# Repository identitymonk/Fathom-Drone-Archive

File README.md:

# Fathom-Drone-Archive
Archive of the dead Fathom Drone Project (https://www.kickstarter.com/projects/1359605477/fathom-one-the-affordable-modular-hd-underwater-dr)

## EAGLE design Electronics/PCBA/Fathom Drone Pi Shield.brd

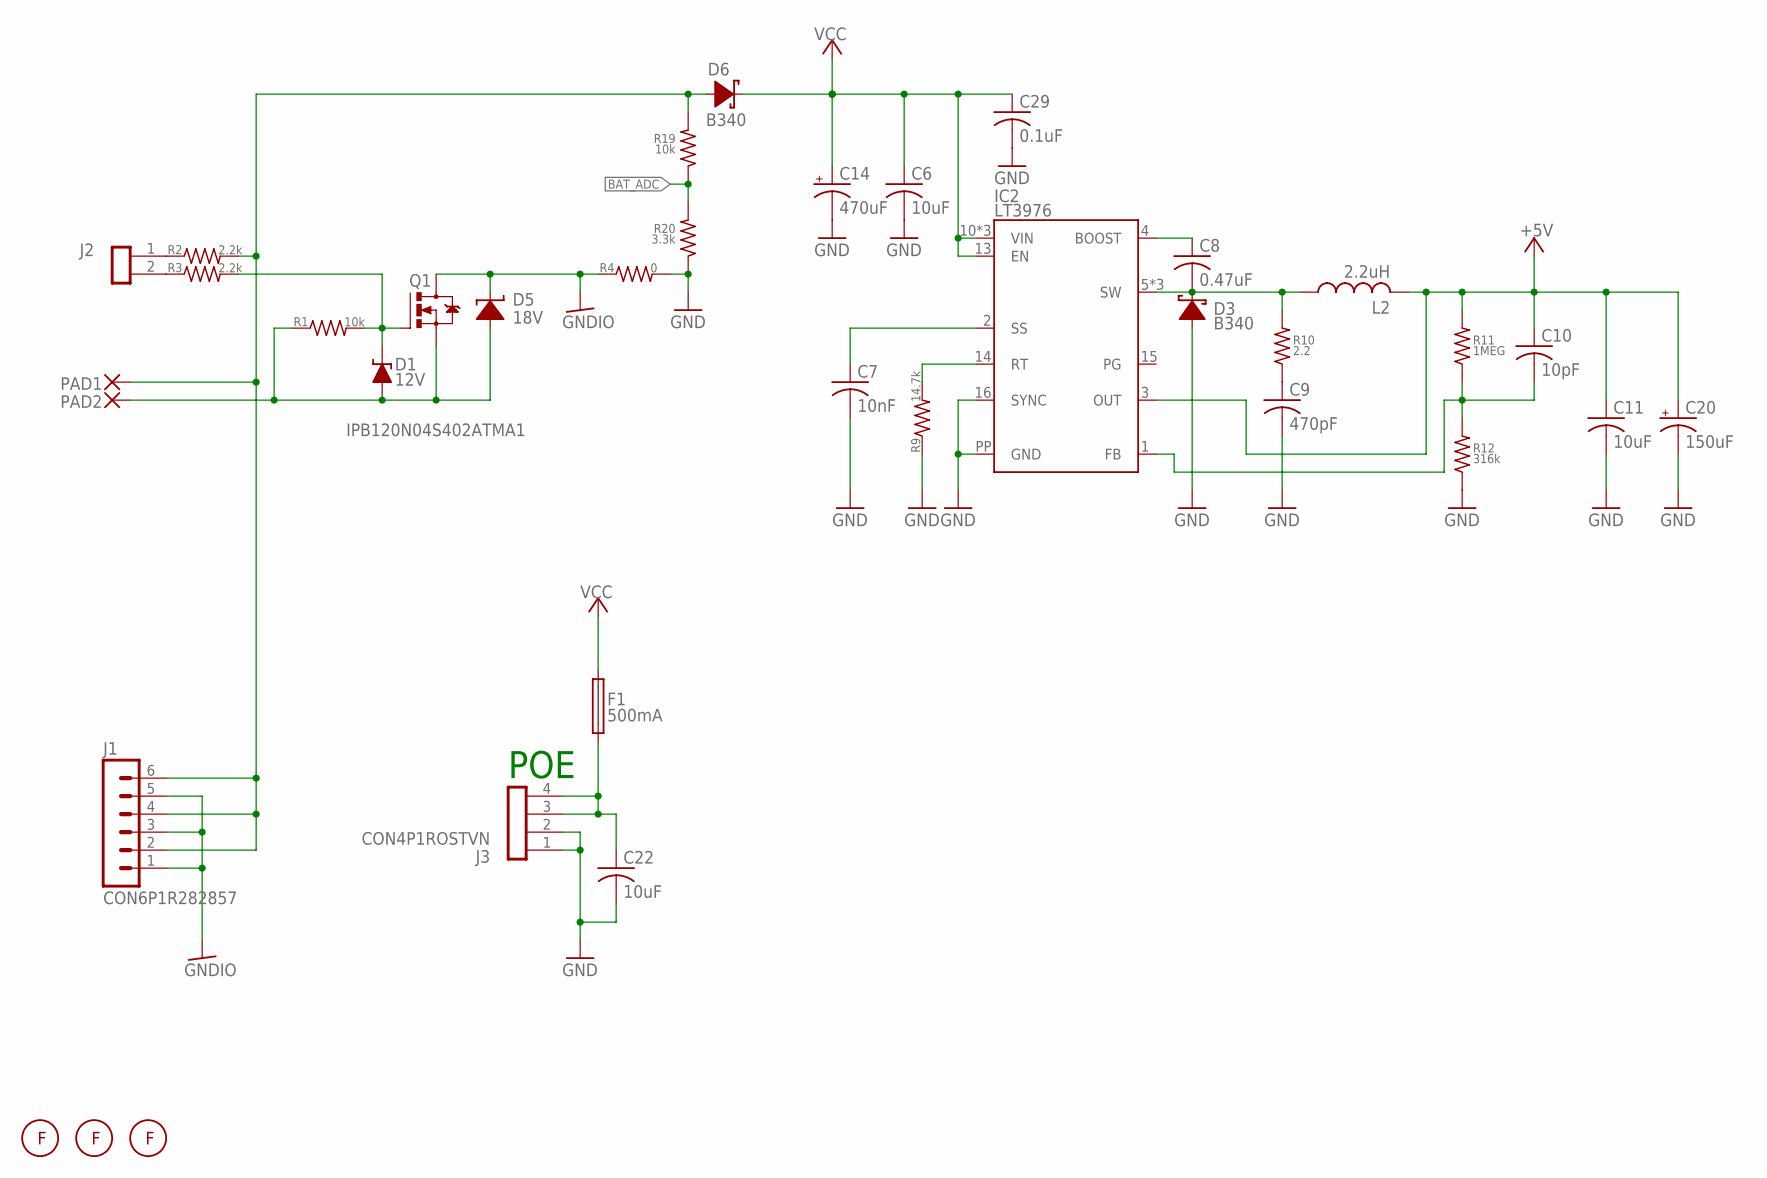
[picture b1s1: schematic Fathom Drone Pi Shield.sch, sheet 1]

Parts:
C6, C22: 10uF; C1206
C7: 10nF; C0402
C8: 0.47uF; C0603
C9: 470pF; C0603
C10: 10pF; C0603
C11: 10uF; C0805
C14: 470uF; E3,5-8
C20: 150uF; PANASONIC_C
C29: 0.1uF; C0402
D1: 12V; SOT-23
D3, D6: B340; SMA
D5: 18V; SMC
F1: 500mA; BETTER_LITTELFUSE1812
FM1, FM2, FM3: FIDUCIAL1MM; 1MMCIRCLE
IC2: LT3976; MSOP-16-PP
J1: CON6P1R282857; 282857-6
J2: CON2P1ROSTVN; OSTVN02A150
J3: CON4P1ROSTVN; OSTVN04A150
L2: 2.2uH; VLP8040
PAD1, PAD2: WIREPAD5.5/3,0; 5.5/3,0
Q1: IPB120N04S402ATMA1; TO263
R1, R19: 10k; R0603
R2, R3: 2.2k; R0603
R4: 0; R0805
R9: 14.7k; R0603
R10: 2.2; R0603
R11: 1MEG; R0603
R12: 316k; R0603
R20: 3.3k; R0402

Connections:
+5V: C10.1, C11.1, C20.+, IC2.3 (OUT), L2.P$2 (2), R11.2; also elsewhere on the board
BAT_ADC: R19.1, R20.2; also elsewhere on the board
GND: C6.2, C7.2, C9.2, C11.2, C14.-, C20.-, C22.2, C29.2, D3.A, IC2.16 (SYNC), IC2.PP (GND), J3.1, J3.2, R4.2, R9.1, R12.1, R20.1; also elsewhere on the board
GNDIO: D5.C, J1.1, J1.3, J1.5, Q1.3 (D), R4.1
unnamed: D1.1 (A), D5.A, PAD2.P$1, Q1.2 (S), R1.1
unnamed: J2.1, R2.1
unnamed: J2.2, R3.1
unnamed: D6.A, J1.2, J1.4, J1.6, PAD1.P$1, R2.2, R19.2
unnamed: C7.1, IC2.2 (SS)
unnamed: IC2.14 (RT), R9.2
unnamed: C8.2, D3.C, IC2.5 (SW), IC2.6 (SW), IC2.7 (SW), L2.P$1 (1), R10.2
unnamed: C8.1, IC2.4 (BOOST)
unnamed: C9.1, R10.1
unnamed: C10.2, IC2.1 (FB), R11.1, R12.2
unnamed: D1.3 (K), Q1.1 (G), R1.2, R3.2
unnamed: C22.1, F1.P$1 (1), J3.3, J3.4
VCC: C6.1, C14.+, C29.1, D6.C, F1.P$2 (2), IC2.10 (VIN), IC2.11 (VIN), IC2.12 (VIN), IC2.13 (EN); also elsewhere on the board

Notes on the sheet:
POE

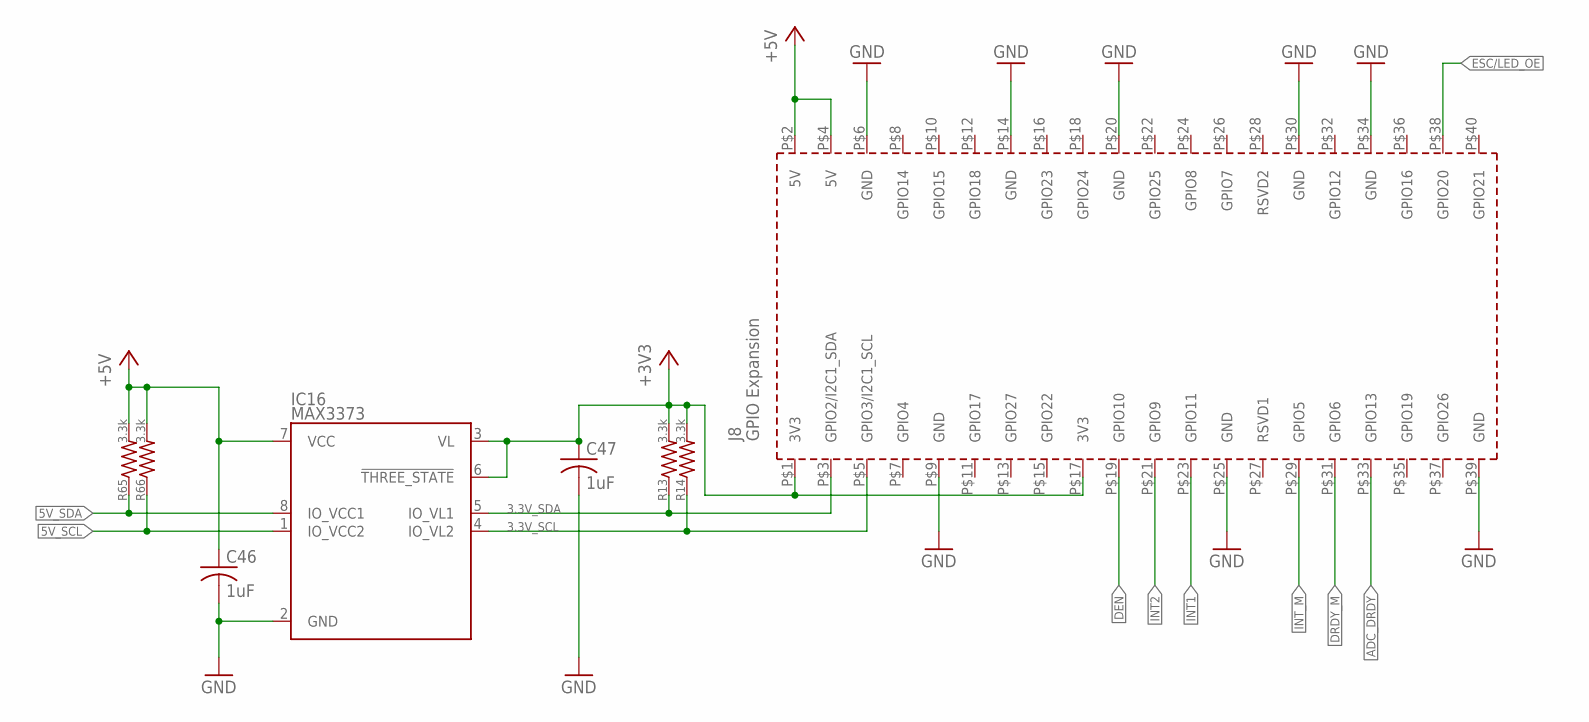
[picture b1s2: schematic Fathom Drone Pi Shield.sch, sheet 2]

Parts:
C46, C47: 1uF; C0402
IC16: MAX3373; TS8
PCB1: RPI3
R13, R14, R65, R66: 3.3k; R0402

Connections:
3.3V_SCL: IC16.4 (IO_VL2), PCB1.P$5 (GPIO3/I2C1_SCL), R14.1; also elsewhere on the board
3.3V_SDA: IC16.5 (IO_VL1), PCB1.P$3 (GPIO2/I2C1_SDA), R13.1; also elsewhere on the board
5V_SCL: IC16.1 (IO_VCC2), R66.1; also elsewhere on the board
5V_SDA: IC16.8 (IO_VCC1), R65.1; also elsewhere on the board
+3V3: C47.1, IC16.3 (VL), IC16.6 (!THREE_STATE), PCB1.P$1 (3V3), PCB1.P$17 (3V3), R13.2, R14.2; also elsewhere on the board
+5V: C46.1, IC16.7 (VCC), PCB1.P$2 (5V), PCB1.P$4 (5V), R65.2, R66.2; also elsewhere on the board
ADC_DRDY: PCB1.P$33 (GPIO13); also elsewhere on the board
DEN: PCB1.P$19 (GPIO10); also elsewhere on the board
DRDY_M: PCB1.P$31 (GPIO6); also elsewhere on the board
ESC/LED_OE: PCB1.P$38 (GPIO20); also elsewhere on the board
GND: C46.2, C47.2, IC16.2 (GND), PCB1.P$6 (GND), PCB1.P$9 (GND), PCB1.P$14 (GND), PCB1.P$20 (GND), PCB1.P$25 (GND), PCB1.P$30 (GND), PCB1.P$34 (GND), PCB1.P$39 (GND); also elsewhere on the board
INT1: PCB1.P$23 (GPIO11); also elsewhere on the board
INT2: PCB1.P$21 (GPIO9); also elsewhere on the board
INT_M: PCB1.P$29 (GPIO5); also elsewhere on the board

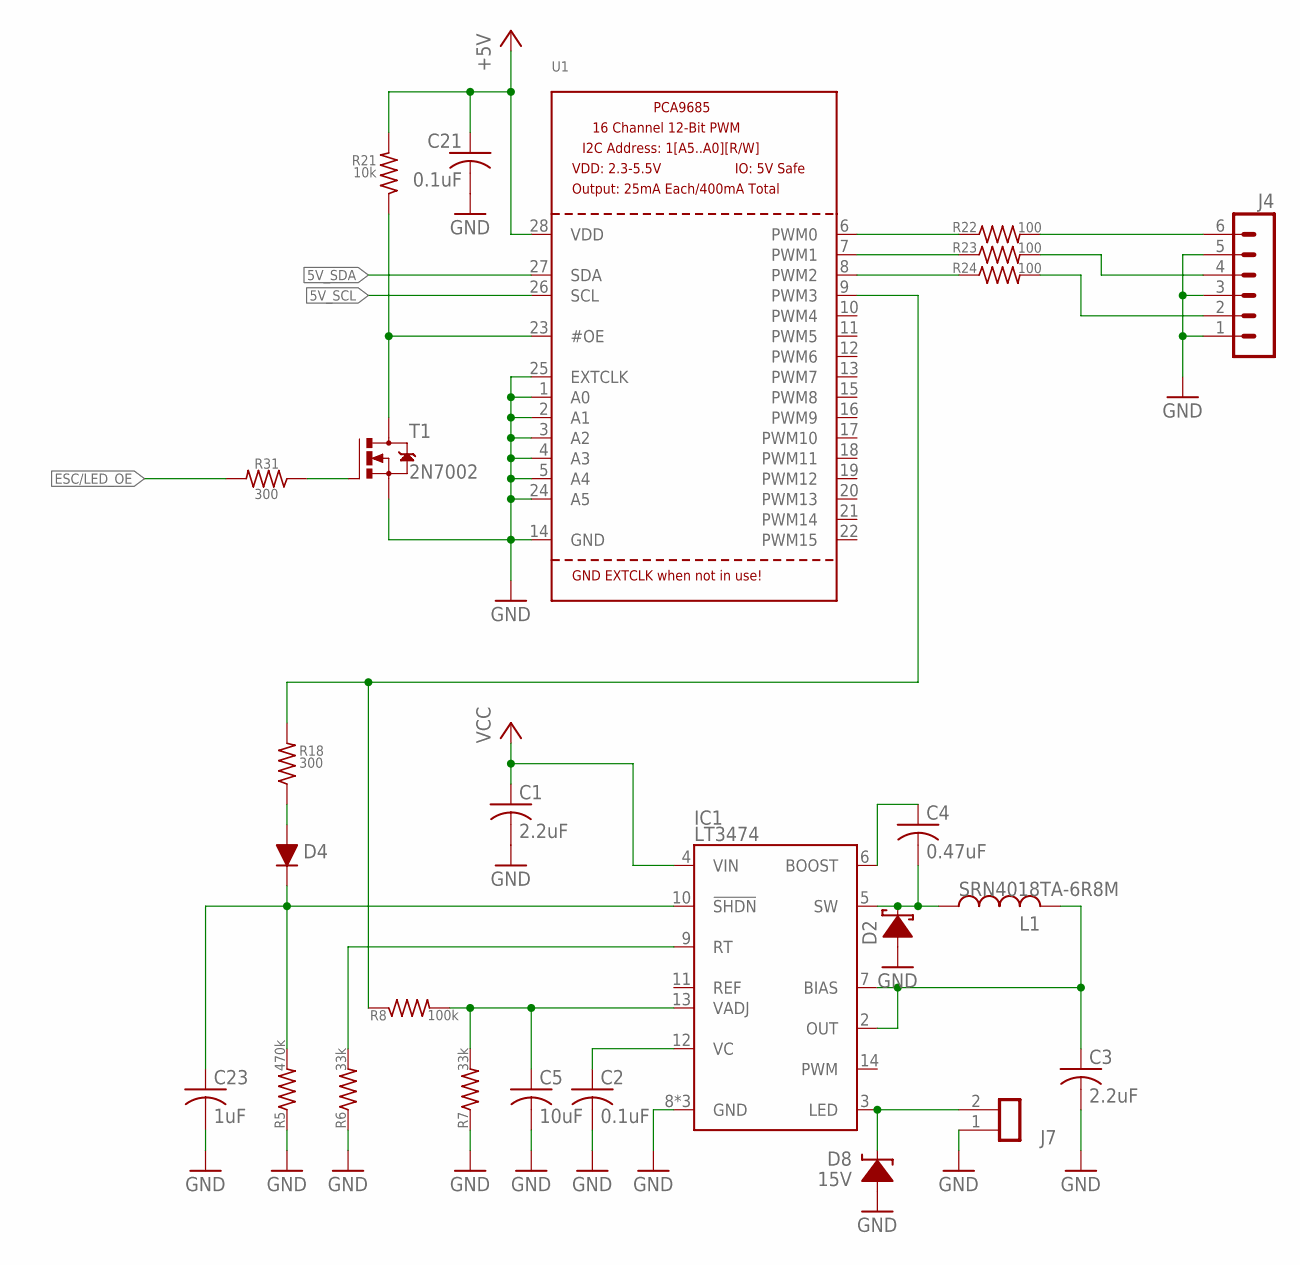
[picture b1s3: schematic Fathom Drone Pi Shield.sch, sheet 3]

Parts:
C1, C3: 2.2uF; C0603
C2, C21: 0.1uF; C0402
C4: 0.47uF; C0603
C5: 10uF; C0805
C23: 1uF; C0402
D2: DIODE-SCHOTTKYSMA; SMA
D4: DIODESOD-123; SOD-123
D8: 15V; SOD123FL
IC1: LT3474; TSSOP16_PP
J4: CON6P1ROSTVN; OSTVN06A150
J7: CON2P1ROSTVN; OSTVN02A150
L1: SRN4018TA-6R8M; L-4026
R5: 470k; R0603
R6, R7: 33k; R0603
R8: 100k; R0603
R18, R31: 300; R0402
R21: 10k; R0603
R22, R23, R24: 100; R0603
T1: 2N7002; SOT-23
U1: PCA9685; TSSOP28

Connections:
5V_SCL: U1.26 (SCL); also elsewhere on the board
5V_SDA: U1.27 (SDA); also elsewhere on the board
+5V: C21.1, R21.2, U1.28 (VDD); also elsewhere on the board
ESC/LED_OE: R31.2; also elsewhere on the board
GND: C1.2, C2.2, C3.2, C5.2, C21.2, C23.2, D2.A, D8.A, IC1.8 (GND), IC1.15 (GND), IC1.PP (GND), J4.1, J4.3, J4.5, J7.1, R5.1, R6.1, R7.1, T1.2 (S), U1.1 (A0), U1.2 (A1), U1.3 (A2), U1.4 (A3), U1.5 (A4), U1.14 (GND), U1.24 (A5), U1.25 (EXTCLK); also elsewhere on the board
unnamed: IC1.9 (RT), R6.2
unnamed: R21.1, T1.3 (D), U1.23 (#OE)
unnamed: C2.1, IC1.12 (VC)
unnamed: D8.K (C), IC1.3 (LED), J7.2
unnamed: C3.1, IC1.2 (OUT), IC1.7 (BIAS), L1.P$2 (2)
unnamed: C4.2, D2.C, IC1.5 (SW), L1.P$1 (1)
unnamed: C4.1, IC1.6 (BOOST)
unnamed: C5.1, IC1.13 (VADJ), R7.2, R8.2
unnamed: R22.1, U1.6 (PWM0)
unnamed: R23.1, U1.7 (PWM1)
unnamed: R24.1, U1.8 (PWM2)
unnamed: R8.1, R18.2, U1.9 (PWM3)
unnamed: J4.6, R22.2
unnamed: J4.4, R23.2
unnamed: J4.2, R24.2
unnamed: C23.1, D4.K, IC1.10 (!SHDN), R5.2
unnamed: D4.A, R18.1
unnamed: R31.1, T1.1 (G)
VCC: C1.1, IC1.4 (VIN); also elsewhere on the board

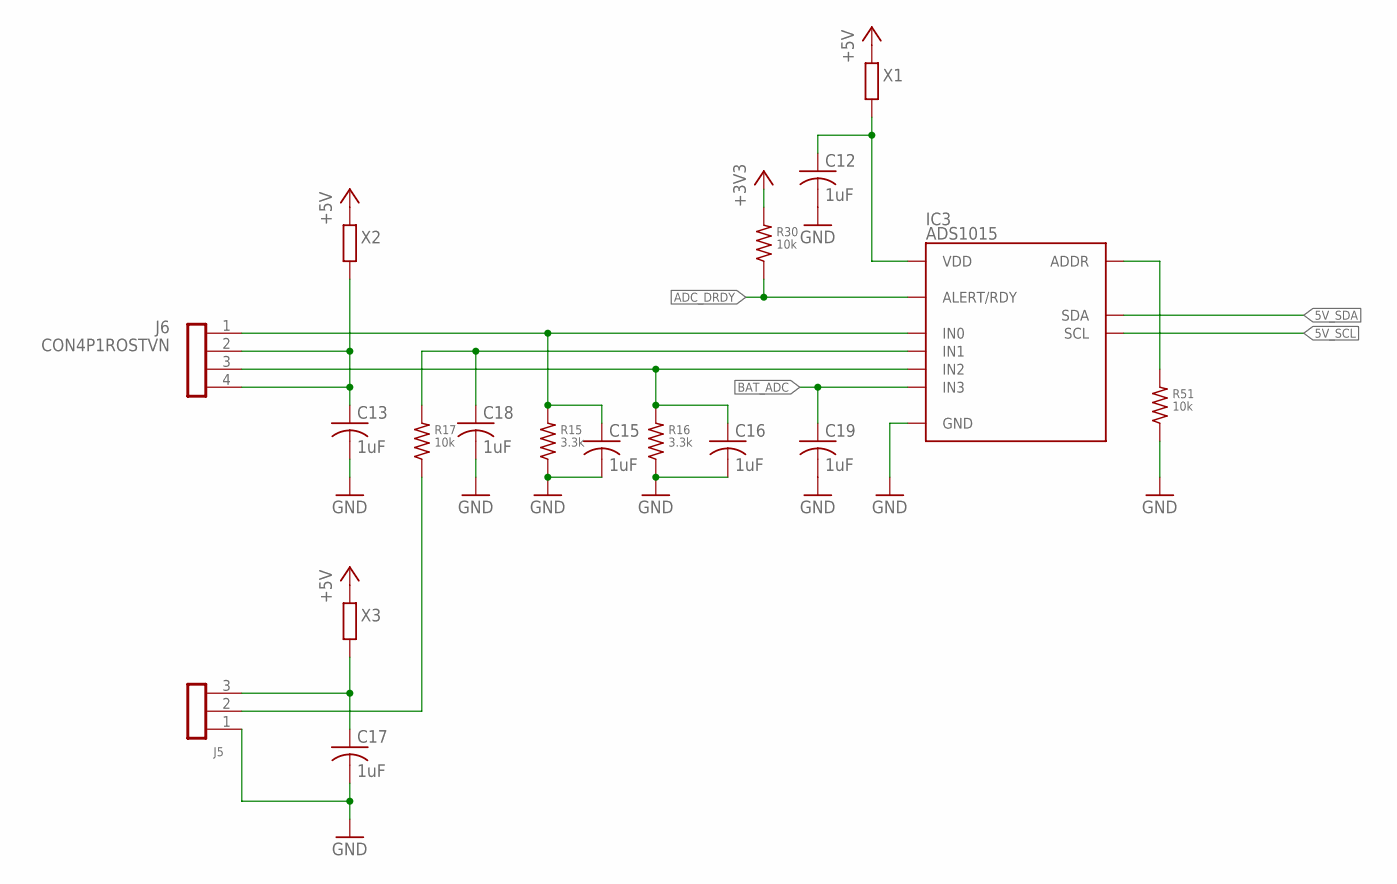
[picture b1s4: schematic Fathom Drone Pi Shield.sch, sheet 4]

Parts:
C12, C13, C15, C16, C17, C18, C19: 1uF; C0402
IC3: ADS1015; MSOP10
J5: CON3P1ROSTVN; OSTVN03A150
J6: CON4P1ROSTVN; OSTVN04A150
R15, R16: 3.3k; R0402
R17, R30, R51: 10k; R0603
X1, X2, X3: PASSIVE0603; R0603@1

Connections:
5V_SCL: IC3.10 (SCL); also elsewhere on the board
5V_SDA: IC3.9 (SDA); also elsewhere on the board
+3V3: R30.2; also elsewhere on the board
+5V: X1.2, X2.2, X3.2; also elsewhere on the board
ADC_DRDY: IC3.2 (ALERT/RDY), R30.1; also elsewhere on the board
BAT_ADC: C19.1, IC3.7 (IN3); also elsewhere on the board
GND: C12.2, C13.2, C15.2, C16.2, C17.2, C18.2, C19.2, IC3.3 (GND), J5.1, R15.1, R16.1, R51.1; also elsewhere on the board
unnamed: C15.1, IC3.4 (IN0), J6.1, R15.2
unnamed: C16.1, IC3.6 (IN2), J6.3, R16.2
unnamed: C13.1, J6.2, J6.4, X2.1
unnamed: C17.1, J5.3, X3.1
unnamed: C12.1, IC3.8 (VDD), X1.1
unnamed: J5.2, R17.1
unnamed: C18.1, IC3.5 (IN1), R17.2
unnamed: IC3.1 (ADDR), R51.2

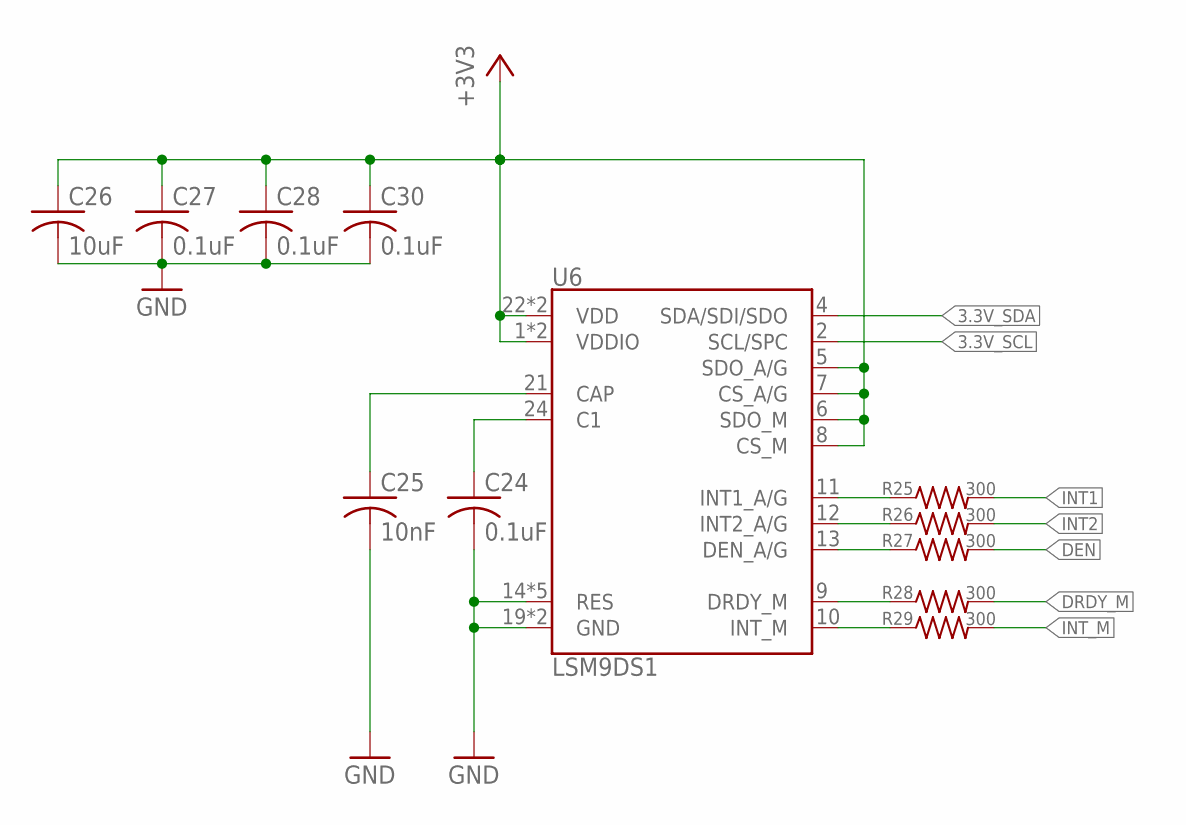
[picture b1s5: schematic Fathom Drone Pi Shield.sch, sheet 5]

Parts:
C24, C27, C28, C30: 0.1uF; C0402
C25: 10nF; C0402
C26: 10uF; C0805
R25, R26, R27, R28, R29: 300; R0402
U6: LSM9DS1; LGA24-8X4

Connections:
3.3V_SCL: U6.2 (SCL/SPC); also elsewhere on the board
3.3V_SDA: U6.4 (SDA/SDI/SDO); also elsewhere on the board
+3V3: C26.1, C27.1, C28.1, C30.1, U6.1 (VDDIO), U6.3 (VDDIO), U6.5 (SDO_A/G), U6.6 (SDO_M), U6.7 (CS_A/G), U6.8 (CS_M), U6.22 (VDD), U6.23 (VDD); also elsewhere on the board
DEN: R27.2; also elsewhere on the board
DRDY_M: R28.2; also elsewhere on the board
GND: C24.2, C25.2, C26.2, C27.2, C28.2, C30.2, U6.14 (RES), U6.15 (RES), U6.16 (RES), U6.17 (RES), U6.18 (RES), U6.19 (GND), U6.20 (GND); also elsewhere on the board
INT1: R25.2; also elsewhere on the board
INT2: R26.2; also elsewhere on the board
INT_M: R29.2; also elsewhere on the board
unnamed: R25.1, U6.11 (INT1_A/G)
unnamed: R26.1, U6.12 (INT2_A/G)
unnamed: R27.1, U6.13 (DEN_A/G)
unnamed: R28.1, U6.9 (DRDY_M)
unnamed: R29.1, U6.10 (INT_M)
unnamed: C24.1, U6.24 (C1)
unnamed: C25.1, U6.21 (CAP)

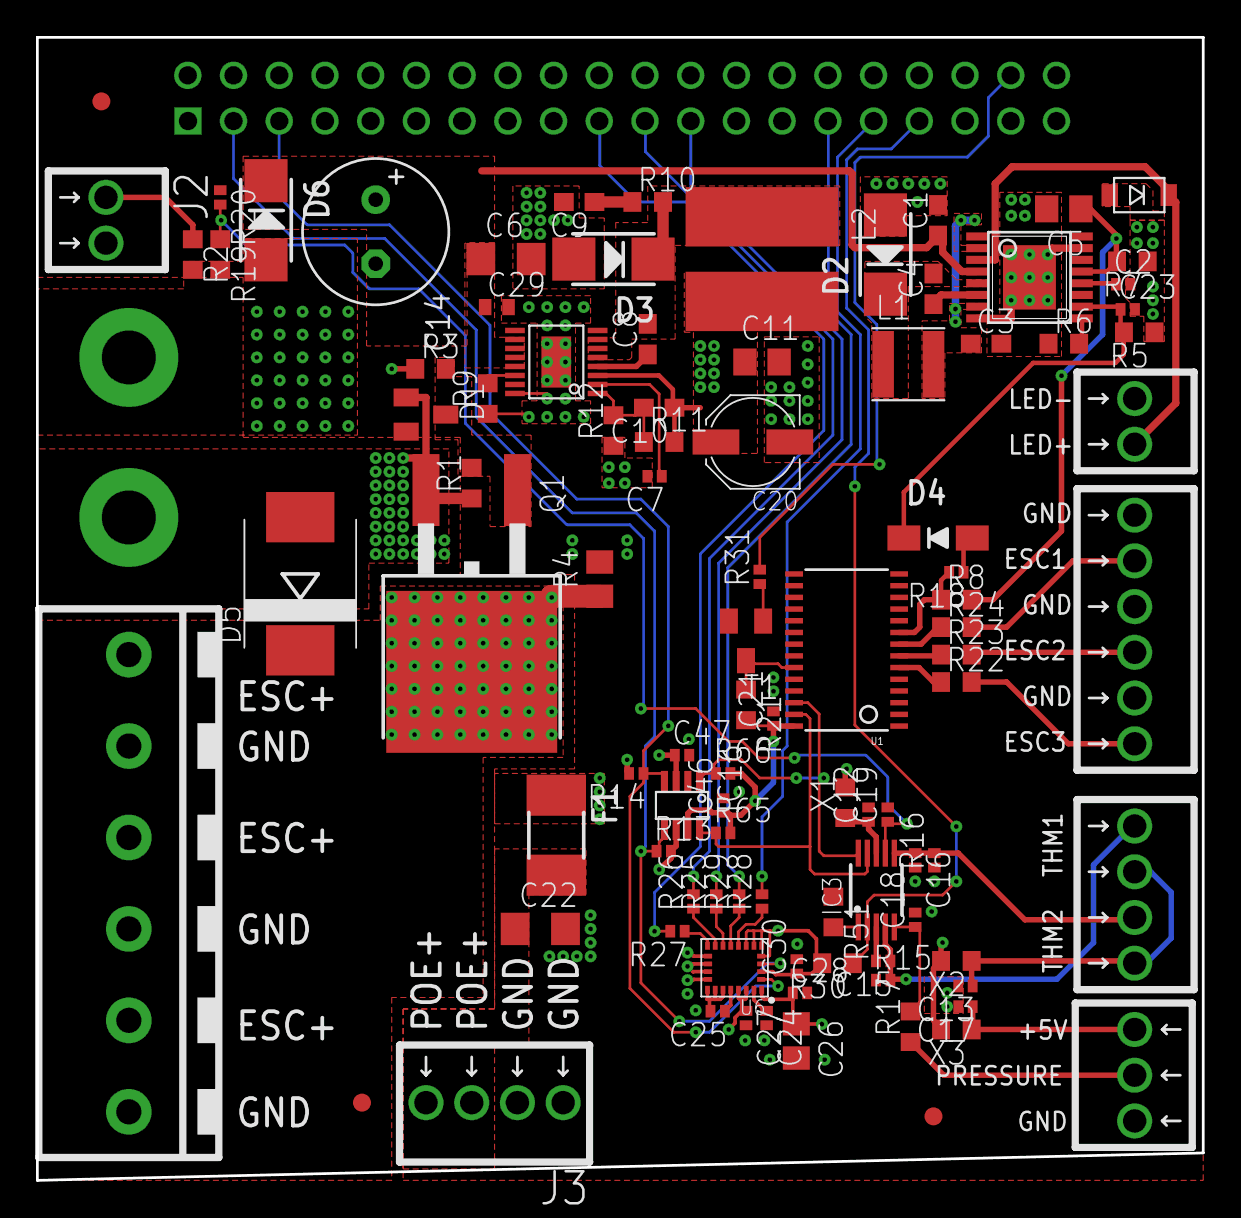
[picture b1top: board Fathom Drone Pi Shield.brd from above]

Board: 4 copper layers, 64.8 x 63.5 mm, 100 parts (0 on the bottom side), 62 nets.

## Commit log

2019-07-11 add1
2019-07-11 +Code
2019-07-11 +Electronics
2019-07-11 +FaceMask
2019-07-11 +PAckaging
2019-07-11 +Potting
2019-07-11 +Renders
2019-07-11 +Assembly
2019-07-11 +App
2019-07-11 + photos
2019-07-11 +Charger
2019-07-11 +Website

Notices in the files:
parts and their libraries:
SparkFun-Sensors: Licensing: Creative Commons ShareAlike 4.0 International - https://creativecommons.org/licenses/by-sa/4.0
